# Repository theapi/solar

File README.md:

Solar
=====

Experiments with solar panels

To set up usb serial communication between the Pi and the Arduino:

Install arduino:
```sudo apt-get install arduino```

Give the pi user permission to use the serial connection:
```sudo usermod -a -G dialout pi```

Optionally install nfs for sharing the data log
From http://www.linuxuser.co.uk/tutorials/building-a-network-of-raspberry-pis

```sudo apt-get install nfs-kernel-server```

Make a shared directory
```sudo mkdir /srv/public```

Edit /etc/exports
```/srv/public *(rw,async,no_subtree_check)```

Ensure rpcbind starts on restart
```sudo update-rc.d rpcbind enable```

Connect to the share with
```
sudo mkdir /mnt/solar
sudo mount <SERVER_IP>:/srv/public /mnt/solar
```

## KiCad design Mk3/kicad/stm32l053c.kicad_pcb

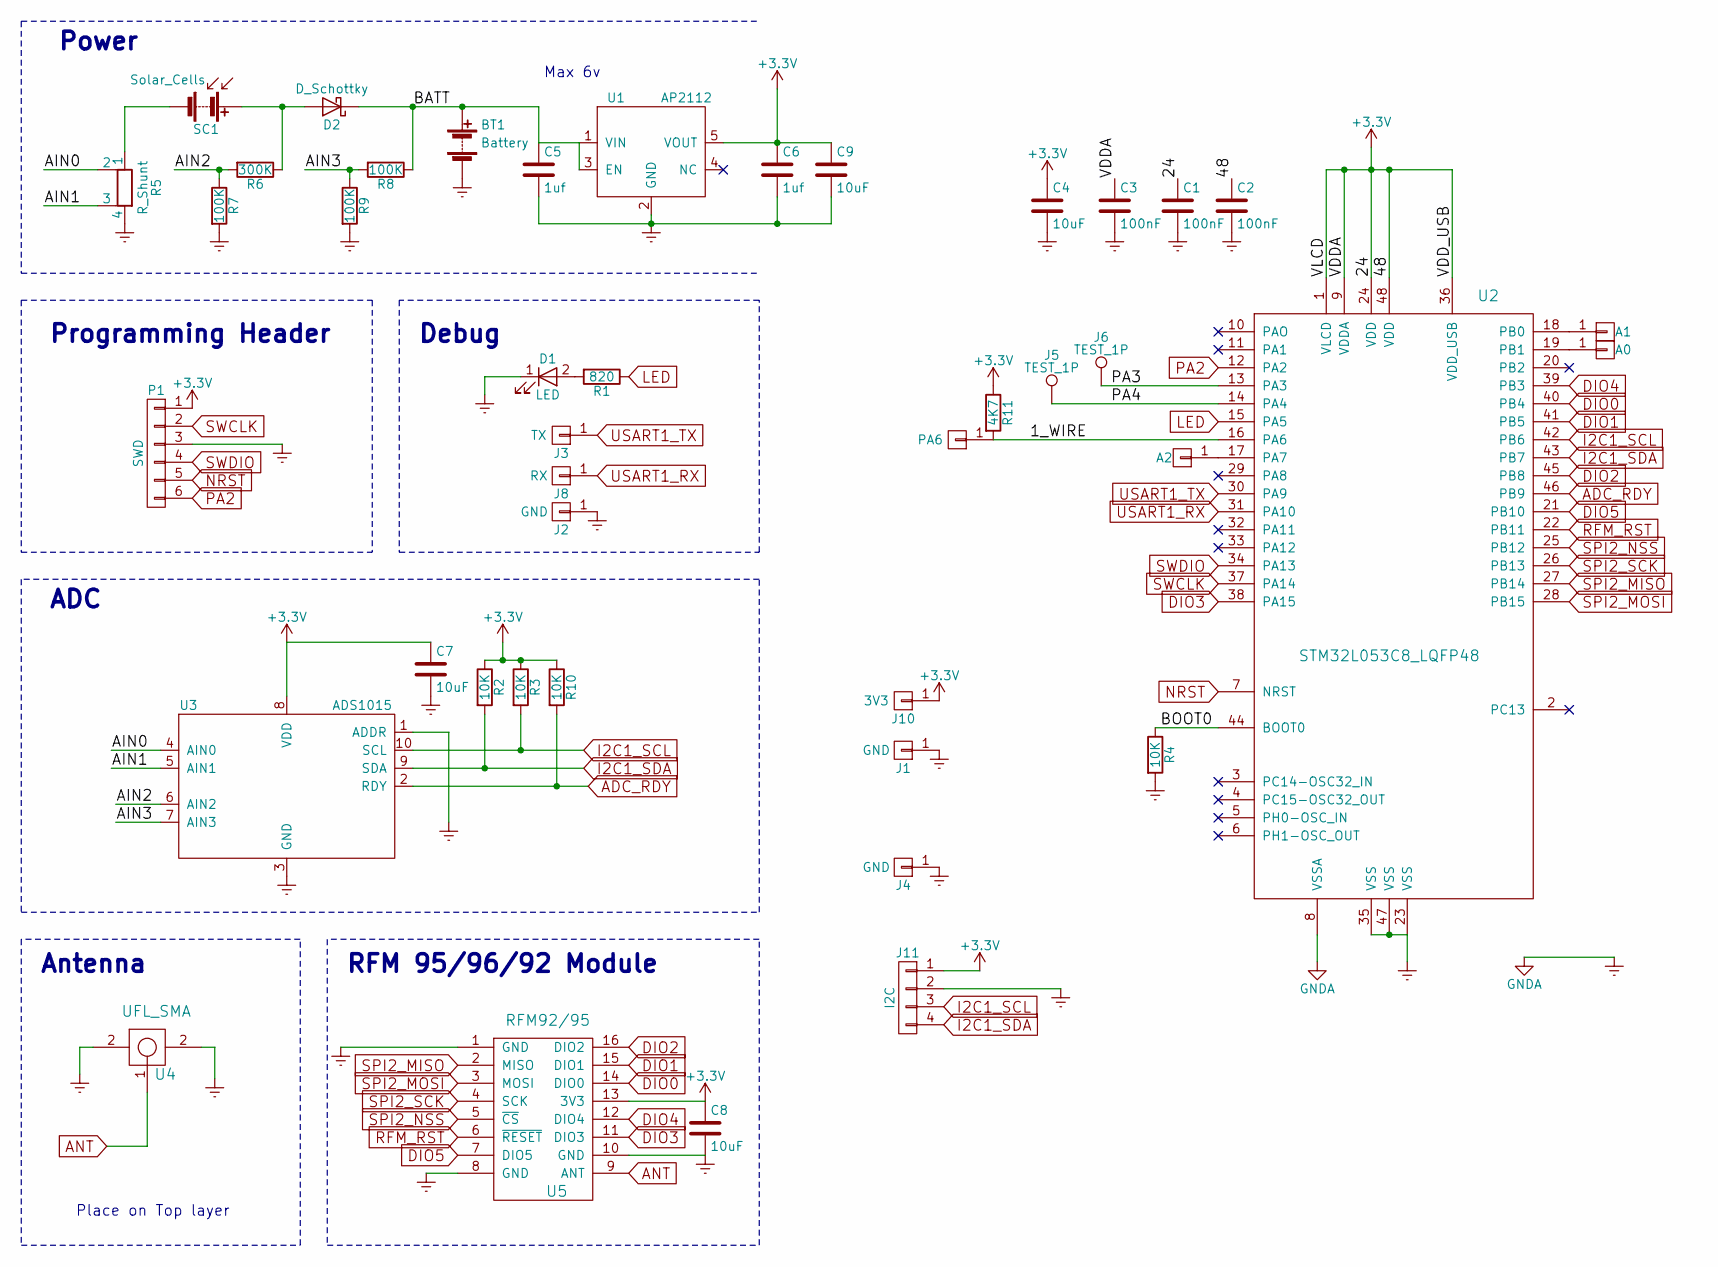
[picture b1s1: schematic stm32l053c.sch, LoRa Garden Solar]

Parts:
A0: A0; Pin_Header_Straight_1x01_Pitch2.54mm
A1: A1; Pin_Header_Straight_1x01_Pitch2.54mm
A2: A2; Pin_Header_Straight_1x01_Pitch2.54mm
BT1: Battery; BatteryBoxAndPins
C1, C2, C3: 100nF; C_0805_HandSoldering
C4, C7, C8, C9: 10uF; C_0805_HandSoldering
C5, C6: 1uf; C_0805_HandSoldering
D1: LED; LED_0805
D2: D_Schottky; D_SOD-323_HandSoldering
J1, J2, J4: GND; Pin_Header_Straight_1x01_Pitch2.54mm
J3: TX; Pin_Header_Straight_1x01_Pitch2.54mm
J5, J6: TEST_1P; TestPoint
J8: RX; Pin_Header_Straight_1x01_Pitch2.54mm
J10: 3V3; Pin_Header_Straight_1x01_Pitch2.54mm
J11: I2C; Pin_Header_Straight_1x04_Pitch2.54mm
P1: SWD; Pin_Header_Straight_1x06_Pitch2.54mm
PA6: A3; Pin_Header_Straight_1x01_Pitch2.54mm
R1: 820; R_0805_HandSoldering
R2, R3, R4, R10: 10K; R_0805_HandSoldering
R5: R_Shunt; SHUNT_1210_HandSoldering
R6: 300K; R_0805_HandSoldering
R7, R8, R9: 100K; R_0805_HandSoldering
R11: 4K7; R_0805_HandSoldering
SC1: Solar_Cells; Pin_Header_Straight_1x02_Pitch2.54mm
U1: AP2112; SOT-23-5_HandSoldering
U2: STM32L053C8_LQFP48; LQFP-48_7x7mm_Pitch0.5mm
U3: ADS1015; TSSOP-10_3x3mm_Pitch0.5mm
U4: UFL_SMA; coaxial_u.fl-r-smt-1
U5: RFM92/95; RFM92_95_96_98; MPN ...

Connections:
+3V3: C1.1, C2.1, C3.1, C4.1, C6.1, C7.1, C8.1, C9.1, J10.1, J11.1, P1.1, R2.1, R3.1, R10.1, R11.1, U1.5 (VOUT), U2.1 (VLCD), U2.9 (VDDA), U2.24 (VDD), U2.36 (VDD_USB), U2.48 (VDD), U3.8 (VDD), U5.13 (3V3)
/1_WIRE: PA6.1, R11.2, U2.16 (PA6)
/AIN0: R5.2, U3.4 (AIN0)
/AIN1: R5.3, U3.5 (AIN1)
/AIN2: R6.2, R7.1, U3.6 (AIN2)
/AIN3: R8.2, R9.1, U3.7 (AIN3)
/BATT: BT1.1 (+), C5.1, D2.1 (K), R8.1, U1.1 (VIN), U1.3 (EN)
/BOOT0: R4.1, U2.44 (BOOT0)
/PA3: J6.1, U2.13 (PA3)
/PA4: J5.1, U2.14 (PA4)
ADC_RDY: R10.2, U2.46 (PB9), U3.2 (RDY)
ANT: U4.1, U5.9 (ANT)
DIO0: U2.40 (PB4), U5.14 (DIO0)
DIO1: U2.41 (PB5), U5.15 (DIO1)
DIO2: U2.45 (PB8), U5.16 (DIO2)
DIO3: U2.38 (PA15), U5.11 (DIO3)
DIO4: U2.39 (PB3), U5.12 (DIO4)
DIO5: U2.21 (PB10), U5.7 (DIO5)
Earth: BT1.2 (-), C1.2, C2.2, C3.2, C4.2, C5.2, C6.2, C7.2, C8.2, C9.2, D1.1 (K), J1.1, J2.1, J4.1, J11.2, P1.3, R4.2, R5.4, R7.2, R9.2, U1.2 (GND), U2.8 (VSSA), U2.23 (VSS), U2.35 (VSS), U2.47 (VSS), U3.1 (ADDR), U3.3 (GND), U4.2, U5.1 (GND), U5.8 (GND), U5.10 (GND)
I2C1_SCL: J11.3, R3.2, U2.42 (PB6), U3.10 (SCL)
I2C1_SDA: J11.4, R2.2, U2.43 (PB7), U3.9 (SDA)
LED: R1.1, U2.15 (PA5)
NRST: P1.5, U2.7 (NRST)
unnamed: A0.1, U2.19 (PB1)
unnamed: A1.1, U2.18 (PB0)
unnamed: A2.1, U2.17 (PA7)
unnamed: D1.2 (A), R1.2
unnamed: D2.2 (A), R6.1, SC1.1 (+)
unnamed: R5.1, SC1.2 (-)
PA2: P1.6, U2.12 (PA2)
RFM_RST: U2.22 (PB11), U5.6 (~RESET)
SPI2_MISO: U2.27 (PB14), U5.2 (MISO)
SPI2_MOSI: U2.28 (PB15), U5.3 (MOSI)
SPI2_NSS: U2.25 (PB12), U5.5 (~CS)
SPI2_SCK: U2.26 (PB13), U5.4 (SCK)
SWCLK: P1.2, U2.37 (PA14)
SWDIO: P1.4, U2.34 (PA13)
USART1_RX: J8.1, U2.31 (PA10)
USART1_TX: J3.1, U2.30 (PA9)

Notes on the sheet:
Antenna
RFM 95/96/92 Module
Place on Top layer
ADC
Programming Header
Power
Max 6v
Debug

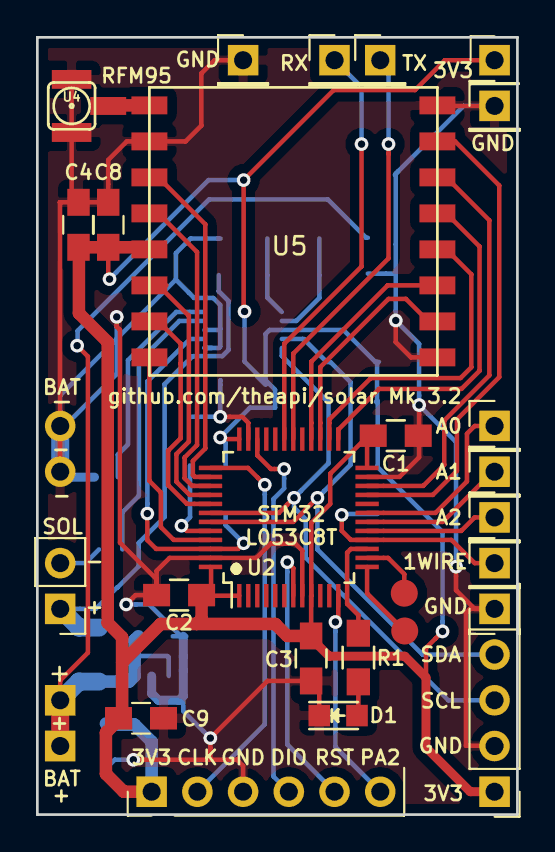
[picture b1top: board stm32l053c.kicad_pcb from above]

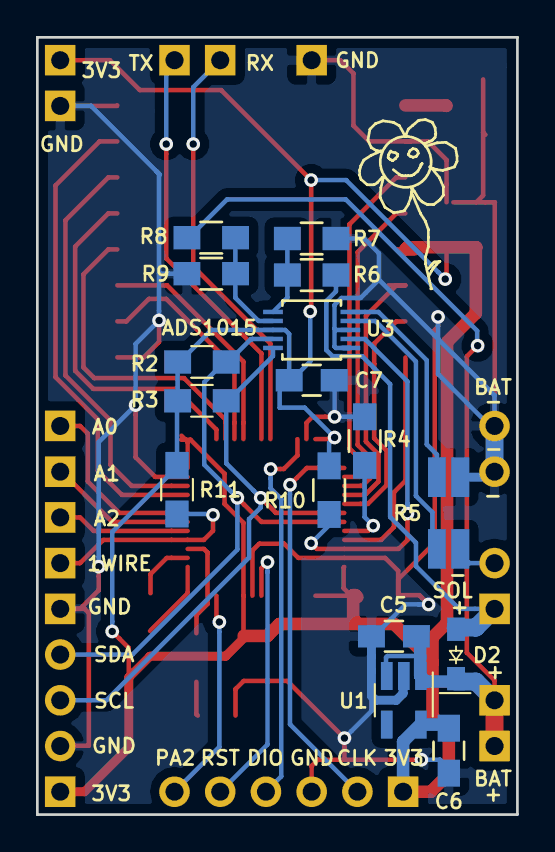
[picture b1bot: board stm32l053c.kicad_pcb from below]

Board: 2 copper layers, 26.7 x 43.2 mm, 43 parts (16 on the bottom side), 39 nets.

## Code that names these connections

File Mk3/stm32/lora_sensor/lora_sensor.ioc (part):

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Mcu.Name=STM32L053C(6-8)Tx
Mcu.Package=LQFP48
Mcu.UserName=STM32L053C8Tx
PA1.GPIOParameters=GPIO_Label
PA1.GPIO_Label=LGT_GND
PA1.Signal=GPIO_Output
PA10.Mode=Asynchronous
PA10.Signal=USART1_RX
PA13.Mode=Serial_Wire
PA13.Signal=SYS_SWDIO
PA14.Mode=Serial_Wire
PA14.Signal=SYS_SWCLK
PA15.GPIOParameters=GPIO_Label
PA15.GPIO_Label=DIO3
PA15.Signal=GPIO_Analog
PA2.Signal=GPIO_Output
PA5.GPIOParameters=GPIO_Label
PA5.GPIO_Label=LED
PA5.Signal=GPIO_Output
PA9.Mode=Asynchronous
PA9.Signal=USART1_TX
PB1.Mode=IN9
PB1.Signal=ADC_IN9
PB10.GPIOParameters=GPIO_Label
PB10.GPIO_Label=DIO5
PB10.Signal=GPIO_Analog
PB12.GPIOParameters=GPIO_Label
PB12.GPIO_Label=SPI2_CS
PB12.Signal=GPIO_Output
PB13.Mode=Full_Duplex_Master
PB13.Signal=SPI2_SCK
PB14.Mode=Full_Duplex_Master
PB14.Signal=SPI2_MISO
PB15.Mode=Full_Duplex_Master
PB15.Signal=SPI2_MOSI
PB3.GPIOParameters=GPIO_Label
PB3.GPIO_Label=DIO4
PB3.Signal=GPIO_Analog
PB4.GPIOParameters=GPIO_Label
PB4.GPIO_Label=DIO0
PB4.Signal=GPXTI4
PB5.GPIOParameters=GPIO_Label
PB5.GPIO_Label=DIO1
PB5.Signal=GPIO_Analog
PB6.Mode=I2C
PB6.Signal=I2C1_SCL
PB7.Mode=I2C
PB7.Signal=I2C1_SDA
PB8.GPIOParameters=GPIO_Label
PB8.GPIO_Label=DI02
PB8.Signal=GPIO_Analog
PB9.GPIOParameters=GPIO_Label
PB9.GPIO_Label=ADC_RDY
PB9.Signal=GPXTI9
PC13.Signal=GPIO_Output
RCC.HSE_VALUE=8000000
RCC.SYSCLKFreq_VALUE=16000000
RCC.SYSCLKSource=RCC_SYSCLKSOURCE_HSI
board=lora_sensor

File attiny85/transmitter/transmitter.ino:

/**
 *
 
Attiny85v
- If not enough light SLEEP.
- Turns on by high on pin interrupt. 
  The pin is attached to the voltage divider that measures the resistance of the LDR. 
  When dark, the voltage is less than the voltage required to register as HIGH.
- Measures the battery voltage. 
- Every minute (may need to reduce this) sends data over RF 
- If battery voltage is high enough, the atmega328p is woken by pin interrupt going HIGH.

 *
 */
 
// ATMEL ATTINY 25/45/85 / ARDUINO
//
//                  +-\/-+
// Ain0 (D 5) PB5  1|    |8  Vcc
// Ain3 (D 3) PB3  2|    |7  PB2 (D 2) Ain1
// Ain2 (D 4) PB4  3|    |6  PB1 (D 1) pwm1
//            GND  4|    |5  PB0 (D 0) pwm0
//                  +----+
// see http://www.gammon.com.au/forum/?id=11488&reply=9#reply9

// i2c http://playground.arduino.cc/Code/USIi2c 
// library from http://playground.arduino.cc/uploads/Code/TinyWireS.zip

 
#include <util/delay.h>
//#include <avr/wdt.h>      // Watchdog
#include <avr/sleep.h>    // Sleep Modes
#include <avr/power.h>    // Power management
#include <VirtualWire.h>

#include <TinyWireS.h>
#include <usiTwiSlave.h>

#define LED_DEBUG 0 
#define PIN_TX 3 // PB3

#define PIN_WAKEUP_MASTER 1 // PB1 Connected to the atmega328 external interupt pin.

#define PIN_WAKEUP_SELF 4   // PB4 / pin 3 / LDR attached
//#define PIN_LDR 2           // PB4 / pin 3 / A2 - NB: ANALOG pin 2 not digital pin 2

//#define THRESHOLD_DARK 200 // A reading below this is considered dark.

#define I2C_SLAVE_ADDR 100

byte msgId = 0;
int ldr_val = 0;

ISR (PCINT0_vect)  
{
  // Wake up
  
}

void setup() 
{
  pinMode(LED_DEBUG, OUTPUT);     
  pinMode(PIN_TX, OUTPUT); 
  pinMode(PIN_WAKEUP_SELF, INPUT);
  pinMode(PIN_WAKEUP_MASTER, OUTPUT); 

  
  digitalWrite(PIN_WAKEUP_MASTER, LOW);

  //TinyWireS.begin(I2C_SLAVE_ADDR);

  // pin change interrupt (example for D4)
  PCMSK  |= bit (PCINT4);  // want pin D4 / pin 3
  GIFR   |= bit (PCIF);    // clear any outstanding interrupts
  GIMSK  |= bit (PCIE);    // enable pin change interrupts  
 
  vw_set_ptt_inverted(true); // Required for DR3100
  vw_setup(2000);      // Bits per sec
  vw_set_tx_pin(PIN_TX);
    
  sei();
  //watchdog_setup();
  
}

void loop()
{
  
  int ldr_val = digitalRead(PIN_WAKEUP_SELF);

  digitalWrite(LED_DEBUG, HIGH);
  
  
  long vcc = readVcc();

  char msg[16];
  sprintf(msg, "%d,%d,%u", msgId, ldr_val, vcc);
  vw_send((uint8_t *)msg, strlen(msg));
  vw_wait_tx(); // Wait until the whole message is gone
  digitalWrite(LED_DEBUG, LOW);
  
  // Reset watchdog so he knows all is well.
  //wdt_reset();

  // @todo Only signal master wake condition if not in SPI mode.
  if (!ldr_val) {
    // Too dark (LDR is reading low)
    // Let atmega328p know it should be asleep
    digitalWrite(PIN_WAKEUP_MASTER, LOW);
    
    // Sleep untill enough light
    goToSleep();
  } else if (vcc >= 3300) {
    // Tell the Atmega328p that it should be awake now.
    digitalWrite(PIN_WAKEUP_MASTER, HIGH);
  }
  
  
  // Cannot use millis() as timer 0 is used by virtualwire on Attiny85
  _delay_ms(1000);

  ++msgId;
  

}


void watchdog_setup()
{
  // Reset after 8 seconds, 
  // unless wdt_reset(); has been successfully called
  //wdt_enable(WDTO_8S);
}



void goToSleep()
{
  digitalWrite(PIN_WAKEUP_MASTER, LOW); // sleep master
  
  set_sleep_mode(SLEEP_MODE_PWR_DOWN);
  cli();
  ADCSRA = 0;            // turn off ADC
  power_all_disable();  // power off ADC, Timer 0 and 1, serial interface
  sleep_enable();
  sleep_bod_disable();
  sei();
  sleep_cpu();                             
  sleep_disable();  
  MCUSR = 0; // clear the reset register 
  power_all_enable();    // power everything back on
  
  ADCSRA = (1 << ADEN); // ADC back on
  
} 


/**
 * Read the internal voltage.
 */
long readVcc() 
{
  // Read 1.1V reference against AVcc
  // set the reference to Vcc and the measurement to the internal 1.1V reference
  #if defined(__AVR_ATmega32U4__) || defined(__AVR_ATmega1280__) || defined(__AVR_ATmega2560__)
    ADMUX = _BV(REFS0) | _BV(MUX4) | _BV(MUX3) | _BV(MUX2) | _BV(MUX1);
  #elif defined (__AVR_ATtiny24__) || defined(__AVR_ATtiny44__) || defined(__AVR_ATtiny84__)
    ADMUX = _BV(MUX5) | _BV(MUX0);
  #elif defined (__AVR_ATtiny25__) || defined(__AVR_ATtiny45__) || defined(__AVR_ATtiny85__)
    ADMUX = _BV(MUX3) | _BV(MUX2);
  #else
    ADMUX = _BV(REFS0) | _BV(MUX3) | _BV(MUX2) | _BV(MUX1);
  #endif  
 
  _delay_ms(2); // Wait for Vref to settle
  ADCSRA |= _BV(ADSC); // Start conversion
  while (bit_is_set(ADCSRA,ADSC)); // measuring
 
  uint8_t low  = ADCL; // must read ADCL first - it then locks ADCH  
  uint8_t high = ADCH; // unlocks both
 
  long result = (high<<8) | low;
 
  result = 1125300L / result; // Calculate Vcc (in mV); 1125300 = 1.1*1023*1000
  return result; // Vcc in millivolts
}

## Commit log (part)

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2014-04-27 ATTiny85 with brown out detector at 2.7v with watchdog checking for cpu freeze every 4 seconds
2014-04-28 Basic data logger
2014-04-28 Cleaner csv
2014-04-28 No need for large message ids, pattern is enough
2014-04-30 Use wdt_reset(); every loop
2014-05-06 Ignore Eclipse
2014-05-06 Initial servo commit
2014-05-06 Track light source
2014-05-07 no delay()
2014-05-07 Use ServoTimer2 so that virtualwire can also be used
2014-05-07 Larger range of movement
2014-05-07 Transmit data
2014-05-08 Start of "too dark" detection
2014-05-10 Use the servo library as it smoother
2014-05-11 Move the servo from pin 10 so it can be used later for SPI
2014-05-11 Speed adjustments
2014-05-12 Start of sleeping
2014-05-12 Read LDR for sleep mode
2014-05-13 Start of i2c
2014-05-13 Upped dark threshold to 600
2014-05-13 Clear watchdog interupt as soon as possible
2014-05-13 i2c demo between Nanos/Unos
2014-05-14 Removed virticle movement
2014-05-14 Communicated with other i2c slave with I2Cserial
2014-05-14 No need to analogRead() the wakeup pin
2014-05-21 SPI pin assignment
2014-05-22 Start of power management
2014-05-22 Wakeup & power
2014-05-23 Watchdog wake from sleep if not dark
2014-05-25 Changed pins & sleep off for now
2014-05-28 attach/detach the servo
2014-05-28 Sleep on INT0 low
2014-05-28 log what is sent from the device
2014-05-28 Do not detach servo, saves power
2014-05-29 Only log data from the solar device
2014-05-29 Data logging fix
2014-05-30 Pat the dog
2014-05-30 Do nothing for about a minute of watchdog wakeups
2014-05-31 Read the solar panel
2014-06-04 Temperature
2014-06-04 Sleep
2014-06-04 Fritzing
2014-06-07 signed ints
2014-06-08 Use vcc for internal temperature calculation
2014-06-08 Calculate as float
2014-06-12 Graphing
2014-07-29 Serial debugging
2014-08-06 Virtualwire to software serial
2014-08-06 Initial message parsing
2014-08-06 Shorted serial print to prevent crash
2014-08-07 PWM using timer 1
2014-08-07 Set pwm value from RF message
2014-08-21 Typo fix
2014-08-25 Use atmega328p
2014-08-27 Mock up of the power board
2014-08-29 PNP to switch voltage regulator
2014-09-01 Power on main board
2014-09-05 RF receiver to serial out
2014-09-15 Debug led
2014-09-16 Wait for the serial data to be sent
2014-09-22 Mmm time to move away from fritzing
2014-09-29 Pwm while sleeping
2014-09-29 Debugging
2014-09-29 Use PWM
2014-09-30 Re-enable timer2 after sleep
2014-10-01 Stand alone
2014-10-02 MCP4725 12 bit DAC as pwm is still buzzing
2014-10-04 Breath
2014-10-08 Use DAC
2014-12-30 Relay the data through the nrf24 radio network
2014-12-30 power_all_enable()
2015-01-01 nrf24 retransmission
2015-01-01 nrf24 datalog
2015-01-01 Handle gibberish in the vcc transmitted value
2015-01-04 Handle negative temperatures
2017-03-24 Tidy up
2017-03-28 Testing feasibility of nrf24 as the radios
2017-04-04 Initial LoRa test
2017-04-04 Init the OLED
2017-04-07 Multiple sensors
2017-04-08 Radiohead library
2017-04-08 LoRa_Radiohead_RX_esp8266
2017-04-08 Start of a speparate data monitor
2017-04-10 Payload
2017-04-10 Start of using a common payload
2017-04-10 Basic OLED layout
2017-04-11 Serial data transfer
2017-04-12 Experiment with nanopb
2017-04-13 Signed ints for negative values
2017-04-13 PHP socket listener
2017-04-13 Ip address on the screen
2017-04-15 Basic socket server & client
2017-04-15 TCP server/client with payload
2017-04-15 Ping TCP clients
2017-04-15 Debug off
2017-04-15 PHP TCP client
2017-04-15 Parse the payload in php
2017-04-15 Handle sudden disconnect faster
2017-04-16 UDP broadcast
2017-04-16 Broadcast UDP socket client
2017-04-16 UDP payload clients
2017-04-16 Broadcast LoRa data via UDP
2017-04-16 Payload start byte
2017-04-17 MQTT
2017-04-18 LEDs on the front panel
2017-04-18 LED front panel
2017-04-20 Different payloads for different payloads
2017-04-21 Namespaced
2017-04-21 Payload for LoRa
2017-04-21 ACK payload
2017-04-23 Rotate screen for the encloseure
2017-04-24 Handle signal payloads
2017-04-24 Set current_payload to the value of the first byte
2017-04-24 Formating
2017-04-24 Serialize with the correct object
2017-04-25 rx_monitor
2017-04-26 AES-128
2017-04-26 AES-128 encryption on radio transmissions
2017-04-27 Faster but shorter distance
2017-04-27 Example configs
2017-05-02 Initial sensor reading
2017-05-03 Current on the OLED
2017-05-05 Removed OLED, and handle slow switching to Internal aref
2017-05-06 Read current on real hardware
2017-05-08 Use the external ADC for the solar panel volts
2017-05-09 Start of Google charts
2017-05-09 Use the websocket data
2017-05-09 Websocket feed
2017-05-13 Control sensor connection
2017-05-13 Temperature sensor
2017-05-13 Power the soil sensor with PIN_SENSOR_VCC
2017-05-15 Guage ranges
2017-05-15 gauge colours
2017-05-17 Show socket connection status
2017-05-18 Start of logging the data to google sheets
2017-05-19 Sleep & no encryption
2017-05-19 Sleep for longer
2017-05-22 Folder restructure
2017-05-22 Log data to Google sheets
2017-05-22 Handle errors
2017-05-22 Example watchdog reset on the stm32L053C8
2017-05-22 Basic led flash with sleep
2017-05-22 8MHz 3 micro amp sleep
2017-05-24 Internal mcu temperature
2017-05-24 Read actual registers
2017-05-25 Vref takes longer to settle
2017-05-29 8MHz external crystal
2017-05-29 8MHz internal
2017-05-30 Start of STM32 board
2017-05-31 Record a timestamp
2017-05-31 3v3 LDO voltage regulator
2017-05-31 Basic pinout
2017-06-01 More connections
2017-06-01 ADC connections
2017-06-01 ADC footprint
2017-06-02 Start of layout
2017-06-02 Initial layout
2017-06-03 Solar charging
2017-06-04 Solar power
2017-06-04 UFL SMA antenna connector
2017-06-05 Layout
2017-06-05 Compact layout + voltage dividers
2017-06-06 Solder mask clearance
2017-06-06 Start of traces
2017-06-06 Initial cubeMX export
2017-06-06 Bigger board
2017-06-06 Routing
2017-06-07 Eclipse project files
2017-06-07 Layout tweaks
2017-06-07 Schematic pdf
2017-06-08 Extra analog inputs
2017-06-08 Blink the LED with sleep
2017-06-09 Corrected analog pin connections
2017-06-09 Labels
2017-06-09 Moved LED to default PA5
2017-06-09 More ground pins
2017-06-11 USART1
2017-06-11 CubeMX project report
2017-06-12 Start of RFM95
2017-06-12 RFM95 defines
2017-06-12 HAL SPI
2017-06-13 Buffer struct
2017-06-13 Use software controlled SPI chip select
2017-06-13 Communicating with RFM95 module
2017-06-14 Arduino example of setting & reading registers on the RFM95
2017-06-14 LoRa init
2017-06-14 RFM95_setMode()
2017-06-14 Some init config
2017-06-15 Update project report
2017-06-17 Connect all the pins of the RFM95 module
2017-06-17 Extra battery pins
2017-06-18 Serial RX
2017-06-19 Start of send()
2017-06-19 RFM95_writeRegisterBurst
2017-06-19 Working transmission
2017-06-19 Ensure LoRa mode is set in RFM95_REG_OP_MODE
2017-06-19 Send the garden payload
2017-06-20 Moved a couple of resistors
2017-06-21 RFM95_TypeDef to hold state
2017-06-21 Sleep as soon as possible
2017-06-21 Start of the main state machine
2017-06-22 Named states
2017-06-22 Formatting
2017-06-22 Register defines
2017-06-22 Function prototypes
2017-06-23 Start of ads1015c functions
2017-06-23 Ported functions
2017-06-23 Style formatting for Eclipse
2017-06-25 Pull up resistor for the DS18B20 one wire temperature sensor
2017-06-27 Shunt footprint change
2017-06-27 I2C read & write
2017-06-28 Tidying ground pads
2017-07-25 Gerbers
2017-07-29 Smoke test for hardware build
2017-07-30 ADS1015
2017-07-30 ADS1015 datasheet
2017-07-30 Working ads1015
2017-07-31 Shift the I2C address to the most signifcant bits
2017-08-03 Measure battery voltage with the external ADC
2017-08-03 I2C header
2017-08-03 I2C power
2017-08-03 Update schematic pdf
2017-08-07 Tweak traces
2017-08-07 Mk3.1 gerbers
2017-08-09 Ready battery data
2017-08-09 Read the battery VCC
2017-08-10 UART transmit only once
2017-08-10 BATTERY_ChargeMv()
2017-08-10 BATTERY_ChargeMa()
2017-08-11 Allow for negative readings
2017-08-11 Temperature files
2017-08-11 Start of lux sensor
2017-08-11 Some defines
2017-08-15 Upgraded CubeMX
2017-08-15 Read votage
2017-08-17 Poll other channels
2017-08-17 Accurate(ish) readings
2017-08-17 Compute the temperature
2017-08-17 Longer sample time
2017-08-24 Solder mask on the voltage regulator
2017-08-24 Larger D2 footprint
2017-08-24 Mk 3.2
2017-08-27 Set RFM95 reset high
2017-08-28 RFM95 off
2017-08-30 Do not use the reset pin (mcu hangs)
2017-08-31 Allow for the module power on reset time
2017-08-31 Pulse the reset line line then float
2017-08-31 Not using the pin interrupt for now as cases problems
2017-09-01 TMP36 temperature sensor
2017-09-04 Take one high res lux reading then power down the lux module
2017-09-06 Unsigned int for lux values
2017-09-07 Sleep for a minute
2017-09-10 OLED layout change
2017-09-10 Longer sample time & take some junk readings
2017-09-10 Adjust dial markings
2017-09-10 ten of a degree temperature
2017-09-11 Moved the reciever
2017-09-12 Float the temperature
2017-09-12 Moved the datalogger
2017-09-12 No front panel leds for now
2017-09-12 dev_pi uses old php
2017-09-20 Show the mA charge on the led panel
2017-09-20 No display when dark
2017-09-20 Disabled MQTT
2018-09-29 Ignore other payloads
2018-10-01 Elasticsearch logger
2018-10-01 Create index with mappings
2018-10-01 Index correction
2018-10-11 Solar payload
2018-10-12 Bit flags
2018-10-12 Unpack to names
2018-10-13 Include the radio signal stats if wanted
2018-10-14 Data size
2018-10-15 Output the doc
2018-10-16 Doc value
2018-10-16 Nolonger output the server response
2018-10-20 Catch all exceptions
2018-10-20 CSV of the data too
2018-10-21 Serial print the radio data
2018-10-21 Handle the radio signal data
2018-10-22 Add the radio signal data to the garden payload
2018-10-22 Datalog the gardne payload with the radio signal data
2018-10-22 UDP payload unserialize in nodejs
2018-10-23 Event handlers
2018-10-23 Full unserialize
2018-10-24 Create an Elasticsearch index
2018-10-24 Allow all scripts to use the UDP port
2018-10-24 Keep a record in a file.
2018-10-25 Garden data to Elasticsearch
2018-10-28 Remove the tab from the UDP message.
2018-11-12 Extract the flags to fields of their own.
2020-03-17 Bump minimist from 1.2.0 to 1.2.5 in /datalogger/nodejs
    Bumps [minimist](https://github.com/substack/minimist) from 1.2.0 to 1.2.5.
    - [Release notes](https://github.com/substack/minimist/releases)
    - [Commits](https://github.com/substack/minimist/compare/1.2.0...1.2.5)
2020-07-16 Bump lodash from 4.17.11 to 4.17.19 in /datalogger/nodejs
    Bumps [lodash](https://github.com/lodash/lodash) from 4.17.11 to 4.17.19.
    - [Release notes](https://github.com/lodash/lodash/releases)
    - [Commits](https://github.com/lodash/lodash/compare/4.17.11...4.17.19)
2021-05-07 Bump lodash from 4.17.11 to 4.17.21 in /datalogger/nodejs
    Bumps [lodash](https://github.com/lodash/lodash) from 4.17.11 to 4.17.21.
    - [Release notes](https://github.com/lodash/lodash/releases)
    - [Commits](https://github.com/lodash/lodash/compare/4.17.11...4.17.21)
2022-02-11 Bump google/protobuf in /Mk2/experiments/protobuf/php
    Bumps [google/protobuf](https://github.com/google/protobuf) from 3.2.1 to 3.15.0.
    - [Release notes](https://github.com/google/protobuf/releases)
    - [Changelog](https://github.com/protocolbuffers/protobuf/blob/master/generate_changelog.py)
    - [Commits](https://github.com/google/protobuf/compare/v3.2.1...v3.15.0)
    ---
    updated-dependencies:
2023-01-01 Bump json5 and config in /datalogger/nodejs
    Bumps [json5](https://github.com/json5/json5) to 2.2.3 and updates ancestor dependency [config](https://github.com/node-config/node-config). These dependencies need to be updated together.
    Updates `json5` from 1.0.1 to 2.2.3
    - [Release notes](https://github.com/json5/json5/releases)
    - [Changelog](https://github.com/json5/json5/blob/main/CHANGELOG.md)
    - [Commits](https://github.com/json5/json5/compare/v1.0.1...v2.2.3)
    Updates `config` from 2.0.1 to 3.3.8
